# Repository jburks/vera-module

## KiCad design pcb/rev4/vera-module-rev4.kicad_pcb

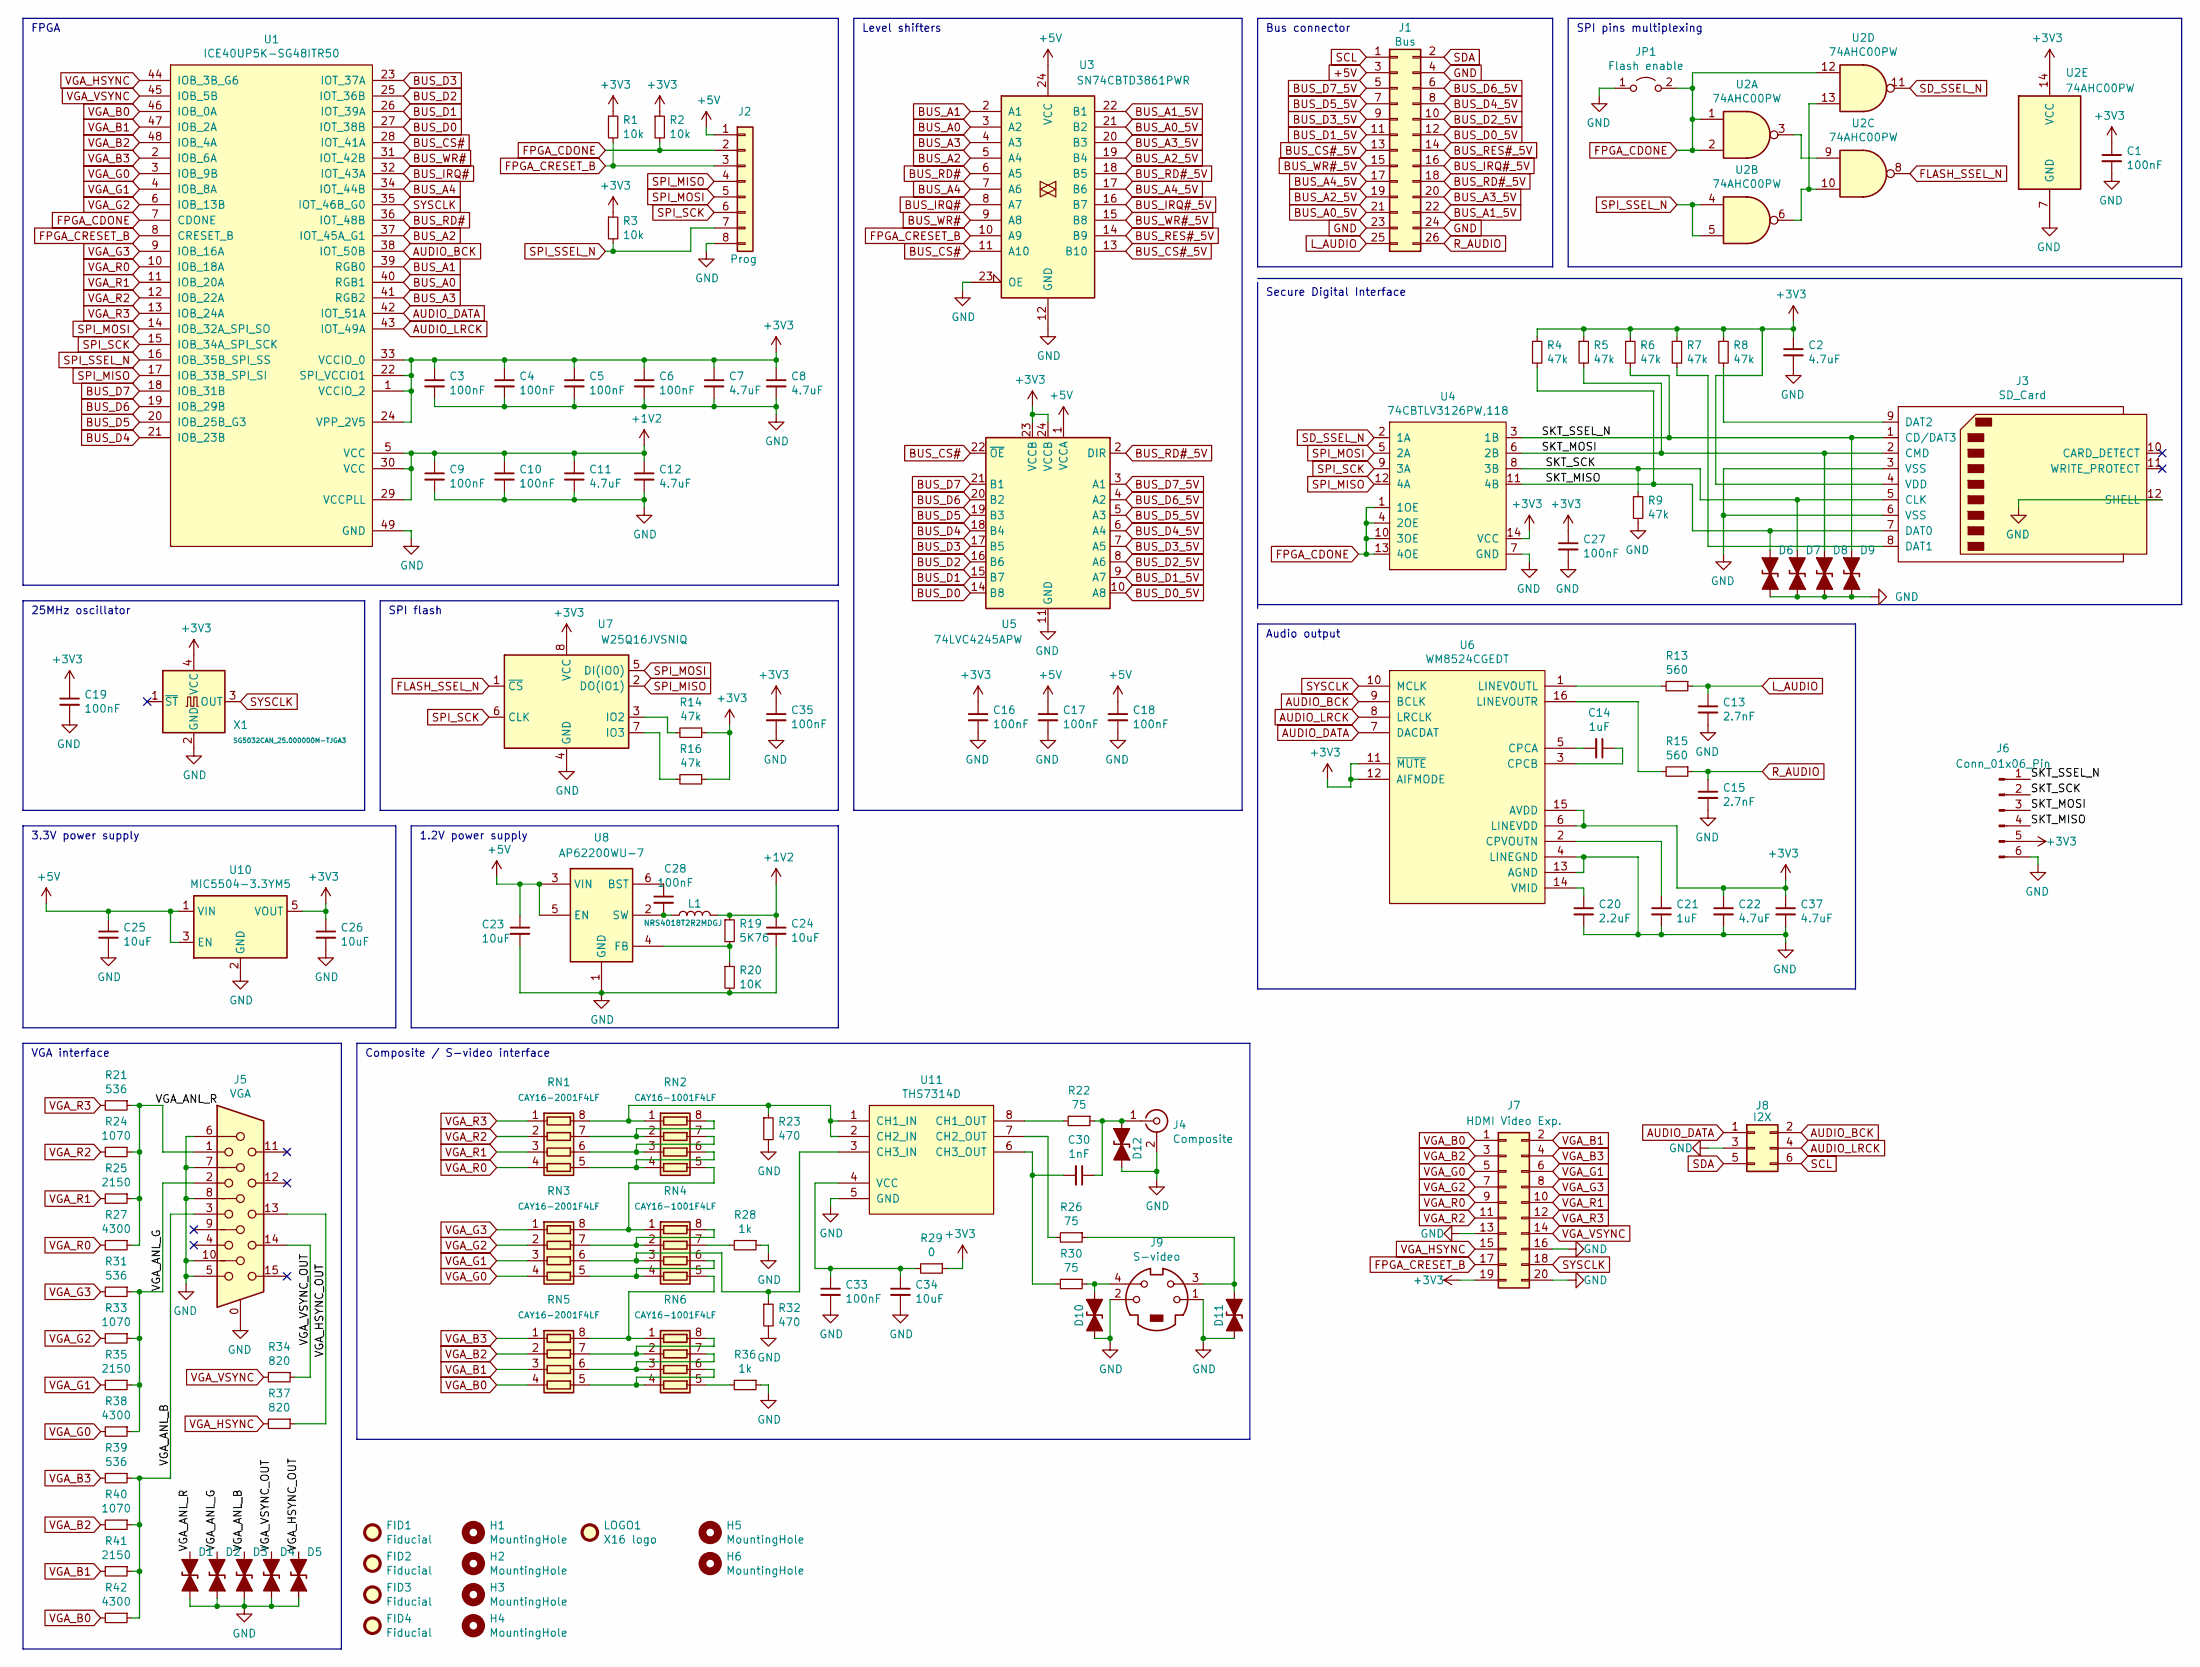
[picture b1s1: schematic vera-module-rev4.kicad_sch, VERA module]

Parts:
C1, C3, C4, C5, C6, C9, C10, C16, C17, C18, C19, C27, C28, C33, C35: 100nF; C_0603_1608Metric
C2, C7, C8, C11, C12, C22, C37: 4.7uF; C_0603_1608Metric
C13, C15: 2.7nF; C_0603_1608Metric
C14, C21: 1uF; C_0603_1608Metric
C20: 2.2uF; C_0603_1608Metric
C23, C24, C25, C26, C34: 10uF; C_0805_2012Metric
C30: 1nF; C_0603_1608Metric
D1, D2, D3, D4, D5, D6, D7, D8, D9, D10, D11, D12: D_TVS_Filled; D_0603_1608Metric
FID1, FID2, FID3, FID4: Fiducial; Fiducial_1mm_Mask2mm
H1, H2, H3, H4: MountingHole; MountingHole_3.2mm_M3
H5, H6: MountingHole; MountingHole_2.2mm_M2
J1: Bus; PinHeader_2x13_P2.54mm_Vertical
J2: Prog; PinHeader_1x08_P2.54mm_Vertical
J3: SD_Card; SD-102
J4: Composite; AV-5
J5: VGA; ICD15S13E4GV00LF
J6: Conn_01x06_Pin; PinHeader_1x06_P2.54mm_Vertical
J7: HDMI Video Exp.; PinSocket_2x10_P2.00mm_Vertical_SMD
J8: I2X; PinSocket_2x03_P2.00mm_Vertical
J9: S-video; MDC-4-02
JP1: Flash enable; PinHeader_1x02_P2.54mm_Vertical
L1: NRS4018T2R2MDGJ; L_Bourns-SRN4018
LOGO1: X16 logo; VERA_CE_Logo2
R1, R2, R3: 10k; R_0603_1608Metric
R4, R5, R6, R7, R8, R9, R14, R16: 47k; R_0603_1608Metric
R13, R15: 560; R_0603_1608Metric
R19: 5K76; R_0603_1608Metric
R20: 10K; R_0603_1608Metric
R21, R31, R39: 536; R_0603_1608Metric
R22, R26, R30: 75; R_0603_1608Metric
R23, R32: 470; R_0603_1608Metric
R24, R33, R40: 1070; R_0603_1608Metric
R25, R35, R41: 2150; R_0603_1608Metric
R27, R38, R42: 4300; R_0603_1608Metric
R28, R36: 1k; R_0603_1608Metric
R29: 0; R_0603_1608Metric
R34, R37: 820; R_0603_1608Metric
RN1, RN3, RN5: CAY16-2001F4LF; R_Array_Convex_4x0603
RN2, RN4, RN6: CAY16-1001F4LF; R_Array_Convex_4x0603
U1: ICE40UP5K-SG48ITR50; QFN-48-1EP_7x7mm_P0.5mm_EP5.3x5.3mm
U2: 74AHC00PW; TSSOP-14_4.4x5mm_P0.65mm
U3: SN74CBTD3861PWR; TSSOP-24_4.4x7.8mm_P0.65mm
U4: 74CBTLV3126PW,118; TSSOP-14_4.4x5mm_P0.65mm
U5: 74LVC4245APW; TSSOP-24_4.4x7.8mm_P0.65mm
U6: WM8524CGEDT; TSSOP-16_4.4x5mm_P0.65mm
U7: W25Q16JVSNIQ; SOIC-8_3.9x4.9mm_P1.27mm
U8: AP62200WU-7; TSOT26-6; Mouser Part Number 621-AP62200WU-7
U10: MIC5504-3.3YM5; SOT-23-5
U11: THS7314D; SOIC-8_3.9x4.9mm_P1.27mm
X1: SG5032CAN_25.000000M-TJGA3; Oscillator_SMD_SeikoEpson_SG8002LB-4Pin_5.0x3.2mm

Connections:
+1V2: C9.1, C10.1, C11.1, C12.1, C24.1, L1.2, R19.1, U1.5 (VCC), U1.29 (VCCPLL), U1.30 (VCC)
+3V3: C1.1, C2.1, C3.1, C4.1, C5.1, C6.1, C7.1, C8.1, C16.1, C19.1, C22.1, C26.1, C27.1, C35.1, C37.1, J3.4 (VDD), J6.5, J7.19, R1.1, R2.1, R3.1, R4.1, R5.1, R6.1, R7.1, R8.1, R14.1, R16.1, R29.1, U1.1 (VCCIO_2), U1.22 (SPI_VCCIO1), U1.24 (VPP_2V5), U1.33 (VCCIO_0), U2.14 (VCC), U4.14 (VCC), U5.23 (VCCB), U5.24 (VCCB), U6.6 (LINEVDD), U6.11 (~MUTE), U6.12 (AIFMODE), U6.15 (AVDD), U7.8 (VCC), U10.5 (VOUT), X1.4 (VCC)
+5V: C17.1, C18.1, C23.1, C25.1, J1.3, J2.1, U3.24 (VCC), U5.1 (VCCA), U8.3 (VIN), U8.5 (EN), U10.1 (VIN), U10.3 (EN)
/SKT_MISO: D6.2 (A2), J3.7 (DAT0), J6.4, R4.2, U4.11 (4B)
/SKT_MOSI: D8.2 (A2), J3.2 (CMD), J6.3, R5.2, U4.6 (2B)
/SKT_SCK: D7.2 (A2), J3.5 (CLK), J6.2, R9.1, U4.8 (3B)
/SKT_SSEL_N: D9.2 (A2), J3.1 (CD/DAT3), J6.1, R6.2, U4.3 (1B)
/VGA_ANL_B: D3.2 (A2), J5.3, R39.1, R40.1, R41.1, R42.1
/VGA_ANL_G: D2.2 (A2), J5.2, R31.1, R33.1, R35.1, R38.1
/VGA_ANL_R: D1.2 (A2), J5.1, R21.1, R24.1, R25.1, R27.1
/VGA_HSYNC_OUT: D5.2 (A2), J5.13, R37.1
/VGA_VSYNC_OUT: D4.2 (A2), J5.14, R34.1
AUDIO_BCK: J8.2, U1.38 (IOT_50B), U6.9 (BCLK)
AUDIO_DATA: J8.1, U1.42 (IOT_51A), U6.7 (DACDAT)
AUDIO_LRCK: J8.4, U1.43 (IOT_49A), U6.8 (LRCLK)
BUS_A0: U1.40 (RGB1), U3.3 (A2)
BUS_A0_5V: J1.21, U3.21 (B2)
BUS_A1: U1.39 (RGB0), U3.2 (A1)
BUS_A1_5V: J1.22, U3.22 (B1)
BUS_A2: U1.37 (IOT_45A_G1), U3.5 (A4)
BUS_A2_5V: J1.19, U3.19 (B4)
BUS_A3: U1.41 (RGB2), U3.4 (A3)
BUS_A3_5V: J1.20, U3.20 (B3)
BUS_A4: U1.34 (IOT_44B), U3.7 (A6)
BUS_A4_5V: J1.17, U3.17 (B6)
BUS_CS#: U1.28 (IOT_41A), U3.11 (A10), U5.22 (~OE)
BUS_CS#_5V: J1.13, U3.13 (B10)
BUS_D0: U1.27 (IOT_38B), U5.14 (B8)
BUS_D0_5V: J1.12, U5.10 (A8)
BUS_D1: U1.26 (IOT_39A), U5.15 (B7)
BUS_D1_5V: J1.11, U5.9 (A7)
BUS_D2: U1.25 (IOT_36B), U5.16 (B6)
BUS_D2_5V: J1.10, U5.8 (A6)
BUS_D3: U1.23 (IOT_37A), U5.17 (B5)
BUS_D3_5V: J1.9, U5.7 (A5)
BUS_D4: U1.21 (IOB_23B), U5.18 (B4)
BUS_D4_5V: J1.8, U5.6 (A4)
BUS_D5: U1.20 (IOB_25B_G3), U5.19 (B3)
BUS_D5_5V: J1.7, U5.5 (A3)
BUS_D6: U1.19 (IOB_29B), U5.20 (B2)
BUS_D6_5V: J1.6, U5.4 (A2)
BUS_D7: U1.18 (IOB_31B), U5.21 (B1)
BUS_D7_5V: J1.5, U5.3 (A1)
BUS_IRQ#: U1.32 (IOT_43A), U3.8 (A7)
BUS_IRQ#_5V: J1.16, U3.16 (B7)
BUS_RD#: U1.36 (IOT_48B), U3.6 (A5)
BUS_RD#_5V: J1.18, U3.18 (B5), U5.2 (DIR)
BUS_RES#_5V: J1.14, U3.14 (B9)
BUS_WR#: U1.31 (IOT_42B), U3.9 (A8)
BUS_WR#_5V: J1.15, U3.15 (B8)
FLASH_SSEL_N: U2.8, U7.1 (~CS)
FPGA_CDONE: J2.2, JP1.2 (B), R2.2, U1.7 (CDONE), U2.1, U2.2, U2.12, U4.1 (1OE), U4.4 (2OE), U4.10 (3OE), U4.13 (4OE)
FPGA_CRESET_B: J2.3, J7.17, R1.2, U1.8 (CRESET_B), U3.10 (A9)
GND: C1.2, C2.2, C3.2, C4.2, C5.2, C6.2, C7.2, C8.2, C9.2, C10.2, C11.2, C12.2, C13.2, C15.2, C16.2, C17.2, C18.2, C19.2, C20.2, C21.2, C22.2, C23.2, C24.2, C25.2, C26.2, C27.2, C33.2, C34.2, C35.2, C37.2, D1.1 (A1), D2.1 (A1), D3.1 (A1), D4.1 (A1), D5.1 (A1), D6.1 (A1), D7.1 (A1), D8.1 (A1), D9.1 (A1), D10.1 (A1), D11.1 (A1), D12.1 (A1), J1.4, J1.23, J1.24, J2.8, J3.3 (VSS), J3.6 (VSS), J3.12 (SHELL), J4.2 (Ext), J5.0, J5.5, J5.6, J5.7, J5.8, J5.10, J6.6, J7.13, J7.16, J7.20, J8.3, J9.1, J9.2, JP1.1 (A), R9.2, R20.2, R23.2, R28.1, R32.2, R36.1, U1.49 (GND), U2.7 (GND), U3.12 (GND), U3.23 (OE), U4.7 (GND), U5.11 (GND), U5.12 (GND), U5.13 (GND), U6.4 (LINEGND), U6.13 (AGND), U7.4 (GND), U8.1 (GND), U10.2 (GND), U11.5 (GND), X1.2 (GND)
L_AUDIO: C13.1, J1.25, R13.1
unnamed: D10.2 (A2), J9.4, R30.1
unnamed: D11.2 (A2), J9.3, R26.1
unnamed: C30.1, D12.2 (A2), J4.1 (In), R22.1
unnamed: J3.8 (DAT1), R7.2
unnamed: J3.9 (DAT2), R8.2
unnamed: R23.1, RN1.8 (R1.2), RN2.1 (R1.1), U11.1 (CH1_IN), U11.2 (CH2_IN)
unnamed: RN1.7 (R2.2), RN2.2 (R2.1), RN2.8 (R1.2)
unnamed: RN1.6 (R3.2), RN2.3 (R3.1), RN2.7 (R2.2)
unnamed: RN1.5 (R4.2), RN2.4 (R4.1), RN2.6 (R3.2)
unnamed: RN2.5 (R4.2), RN3.8 (R1.2), RN4.1 (R1.1)
unnamed: RN3.7 (R2.2), RN4.2 (R2.1), RN4.8 (R1.2)
unnamed: R32.1, RN3.6 (R3.2), RN4.3 (R3.1), U11.3 (CH3_IN)
unnamed: RN3.5 (R4.2), RN4.4 (R4.1), RN4.6 (R3.2)
unnamed: R28.2, RN4.7 (R2.2)
unnamed: RN4.5 (R4.2), RN5.8 (R1.2), RN6.1 (R1.1)
unnamed: RN5.7 (R2.2), RN6.2 (R2.1), RN6.8 (R1.2)
unnamed: RN5.6 (R3.2), RN6.3 (R3.1), RN6.7 (R2.2)
unnamed: RN5.5 (R4.2), RN6.4 (R4.1), RN6.6 (R3.2)
unnamed: R36.2, RN6.5 (R4.2)
unnamed: U2.3, U2.9
unnamed: U2.6, U2.10, U2.13
unnamed: C14.2, U6.5 (CPCA)
unnamed: C14.1, U6.3 (CPCB)
unnamed: C21.1, U6.2 (CPVOUTN)
unnamed: R13.2, U6.1 (LINEVOUTL)
unnamed: R15.2, U6.16 (LINEVOUTR)
unnamed: C20.1, U6.14 (VMID)
unnamed: R14.2, U7.3 (IO2)
unnamed: R16.2, U7.7 (IO3)
unnamed: C28.1, U8.6 (BST)
unnamed: R19.2, R20.1, U8.4 (FB)
unnamed: C28.2, L1.1, U8.2 (SW)
unnamed: R22.2, U11.8 (CH1_OUT)
unnamed: R26.2, U11.7 (CH2_OUT)
unnamed: C30.2, R30.2, U11.6 (CH3_OUT)
unnamed: C33.1, C34.1, R29.2, U11.4 (VCC)
R_AUDIO: C15.1, J1.26, R15.1
SCL: J1.1, J8.6
SDA: J1.2, J8.5
SD_SSEL_N: U2.11, U4.2 (1A)
SPI_MISO: J2.4, U1.17 (IOB_33B_SPI_SI), U4.12 (4A), U7.2 (DO(IO1))
SPI_MOSI: J2.5, U1.14 (IOB_32A_SPI_SO), U4.5 (2A), U7.5 (DI(IO0))
SPI_SCK: J2.6, U1.15 (IOB_34A_SPI_SCK), U4.9 (3A), U7.6 (CLK)
SPI_SSEL_N: J2.7, R3.2, U1.16 (IOB_35B_SPI_SS), U2.4, U2.5
SYSCLK: J7.18, U1.35 (IOT_46B_G0), U6.10 (MCLK), X1.3 (OUT)
VGA_B0: J7.1, R42.2, RN5.4 (R4.1), U1.46 (IOB_0A)
VGA_B1: J7.2, R41.2, RN5.3 (R3.1), U1.47 (IOB_2A)
VGA_B2: J7.3, R40.2, RN5.2 (R2.1), U1.48 (IOB_4A)
VGA_B3: J7.4, R39.2, RN5.1 (R1.1), U1.2 (IOB_6A)
VGA_G0: J7.5, R38.2, RN3.4 (R4.1), U1.3 (IOB_9B)
VGA_G1: J7.6, R35.2, RN3.3 (R3.1), U1.4 (IOB_8A)
VGA_G2: J7.7, R33.2, RN3.2 (R2.1), U1.6 (IOB_13B)
VGA_G3: J7.8, R31.2, RN3.1 (R1.1), U1.9 (IOB_16A)
VGA_HSYNC: J7.15, R37.2, U1.44 (IOB_3B_G6)
VGA_R0: J7.9, R27.2, RN1.4 (R4.1), U1.10 (IOB_18A)
VGA_R1: J7.10, R25.2, RN1.3 (R3.1), U1.11 (IOB_20A)
VGA_R2: J7.11, R24.2, RN1.2 (R2.1), U1.12 (IOB_22A)
VGA_R3: J7.12, R21.2, RN1.1 (R1.1), U1.13 (IOB_24A)
VGA_VSYNC: J7.14, R34.2, U1.45 (IOB_5B)

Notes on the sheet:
Composite / S-video interface
1.2V power supply
25MHz oscillator
Secure Digital Interface
3.3V power supply
Audio output
SPI flash
FPGA
SPI pins multiplexing
Level shifters
VGA interface
Bus connector

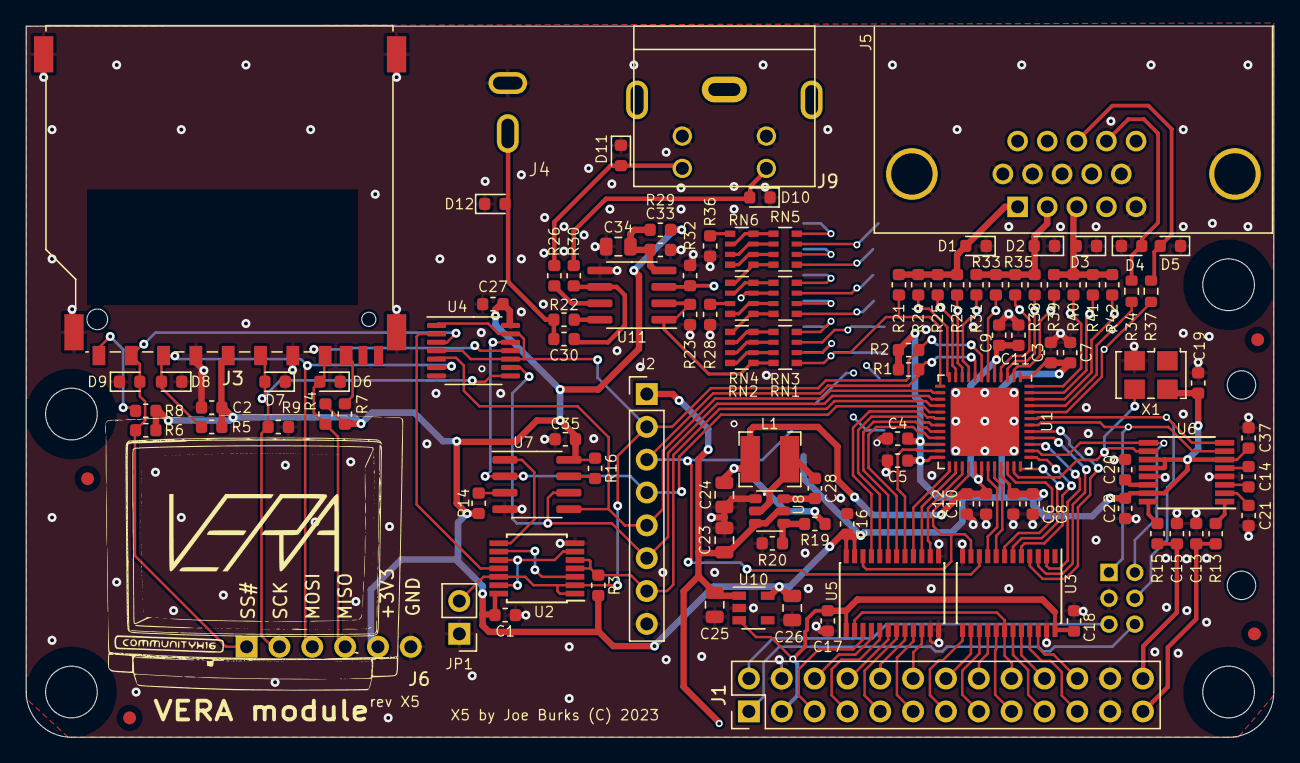
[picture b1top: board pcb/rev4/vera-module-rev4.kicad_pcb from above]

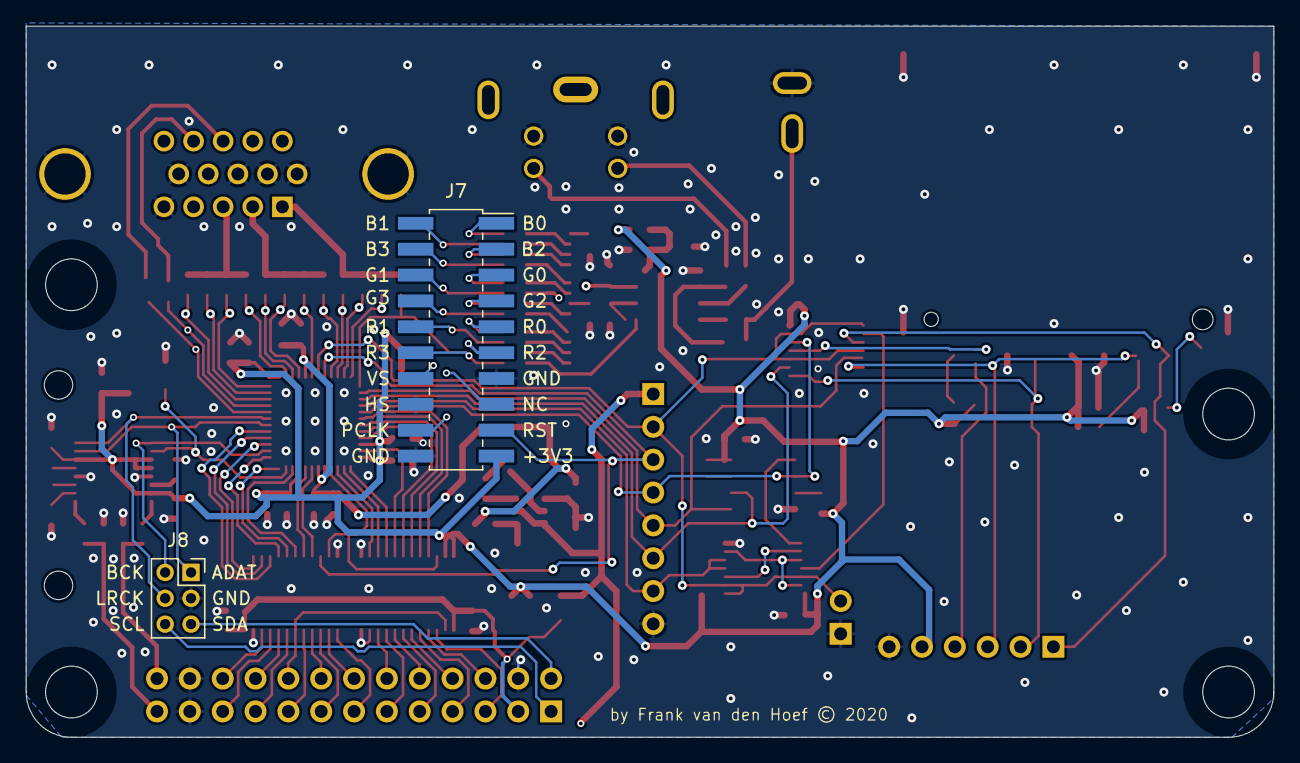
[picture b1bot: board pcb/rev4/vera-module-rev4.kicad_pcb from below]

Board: 4 copper layers, 96.5 x 55.0 mm, 121 parts (2 on the bottom side), 114 nets.

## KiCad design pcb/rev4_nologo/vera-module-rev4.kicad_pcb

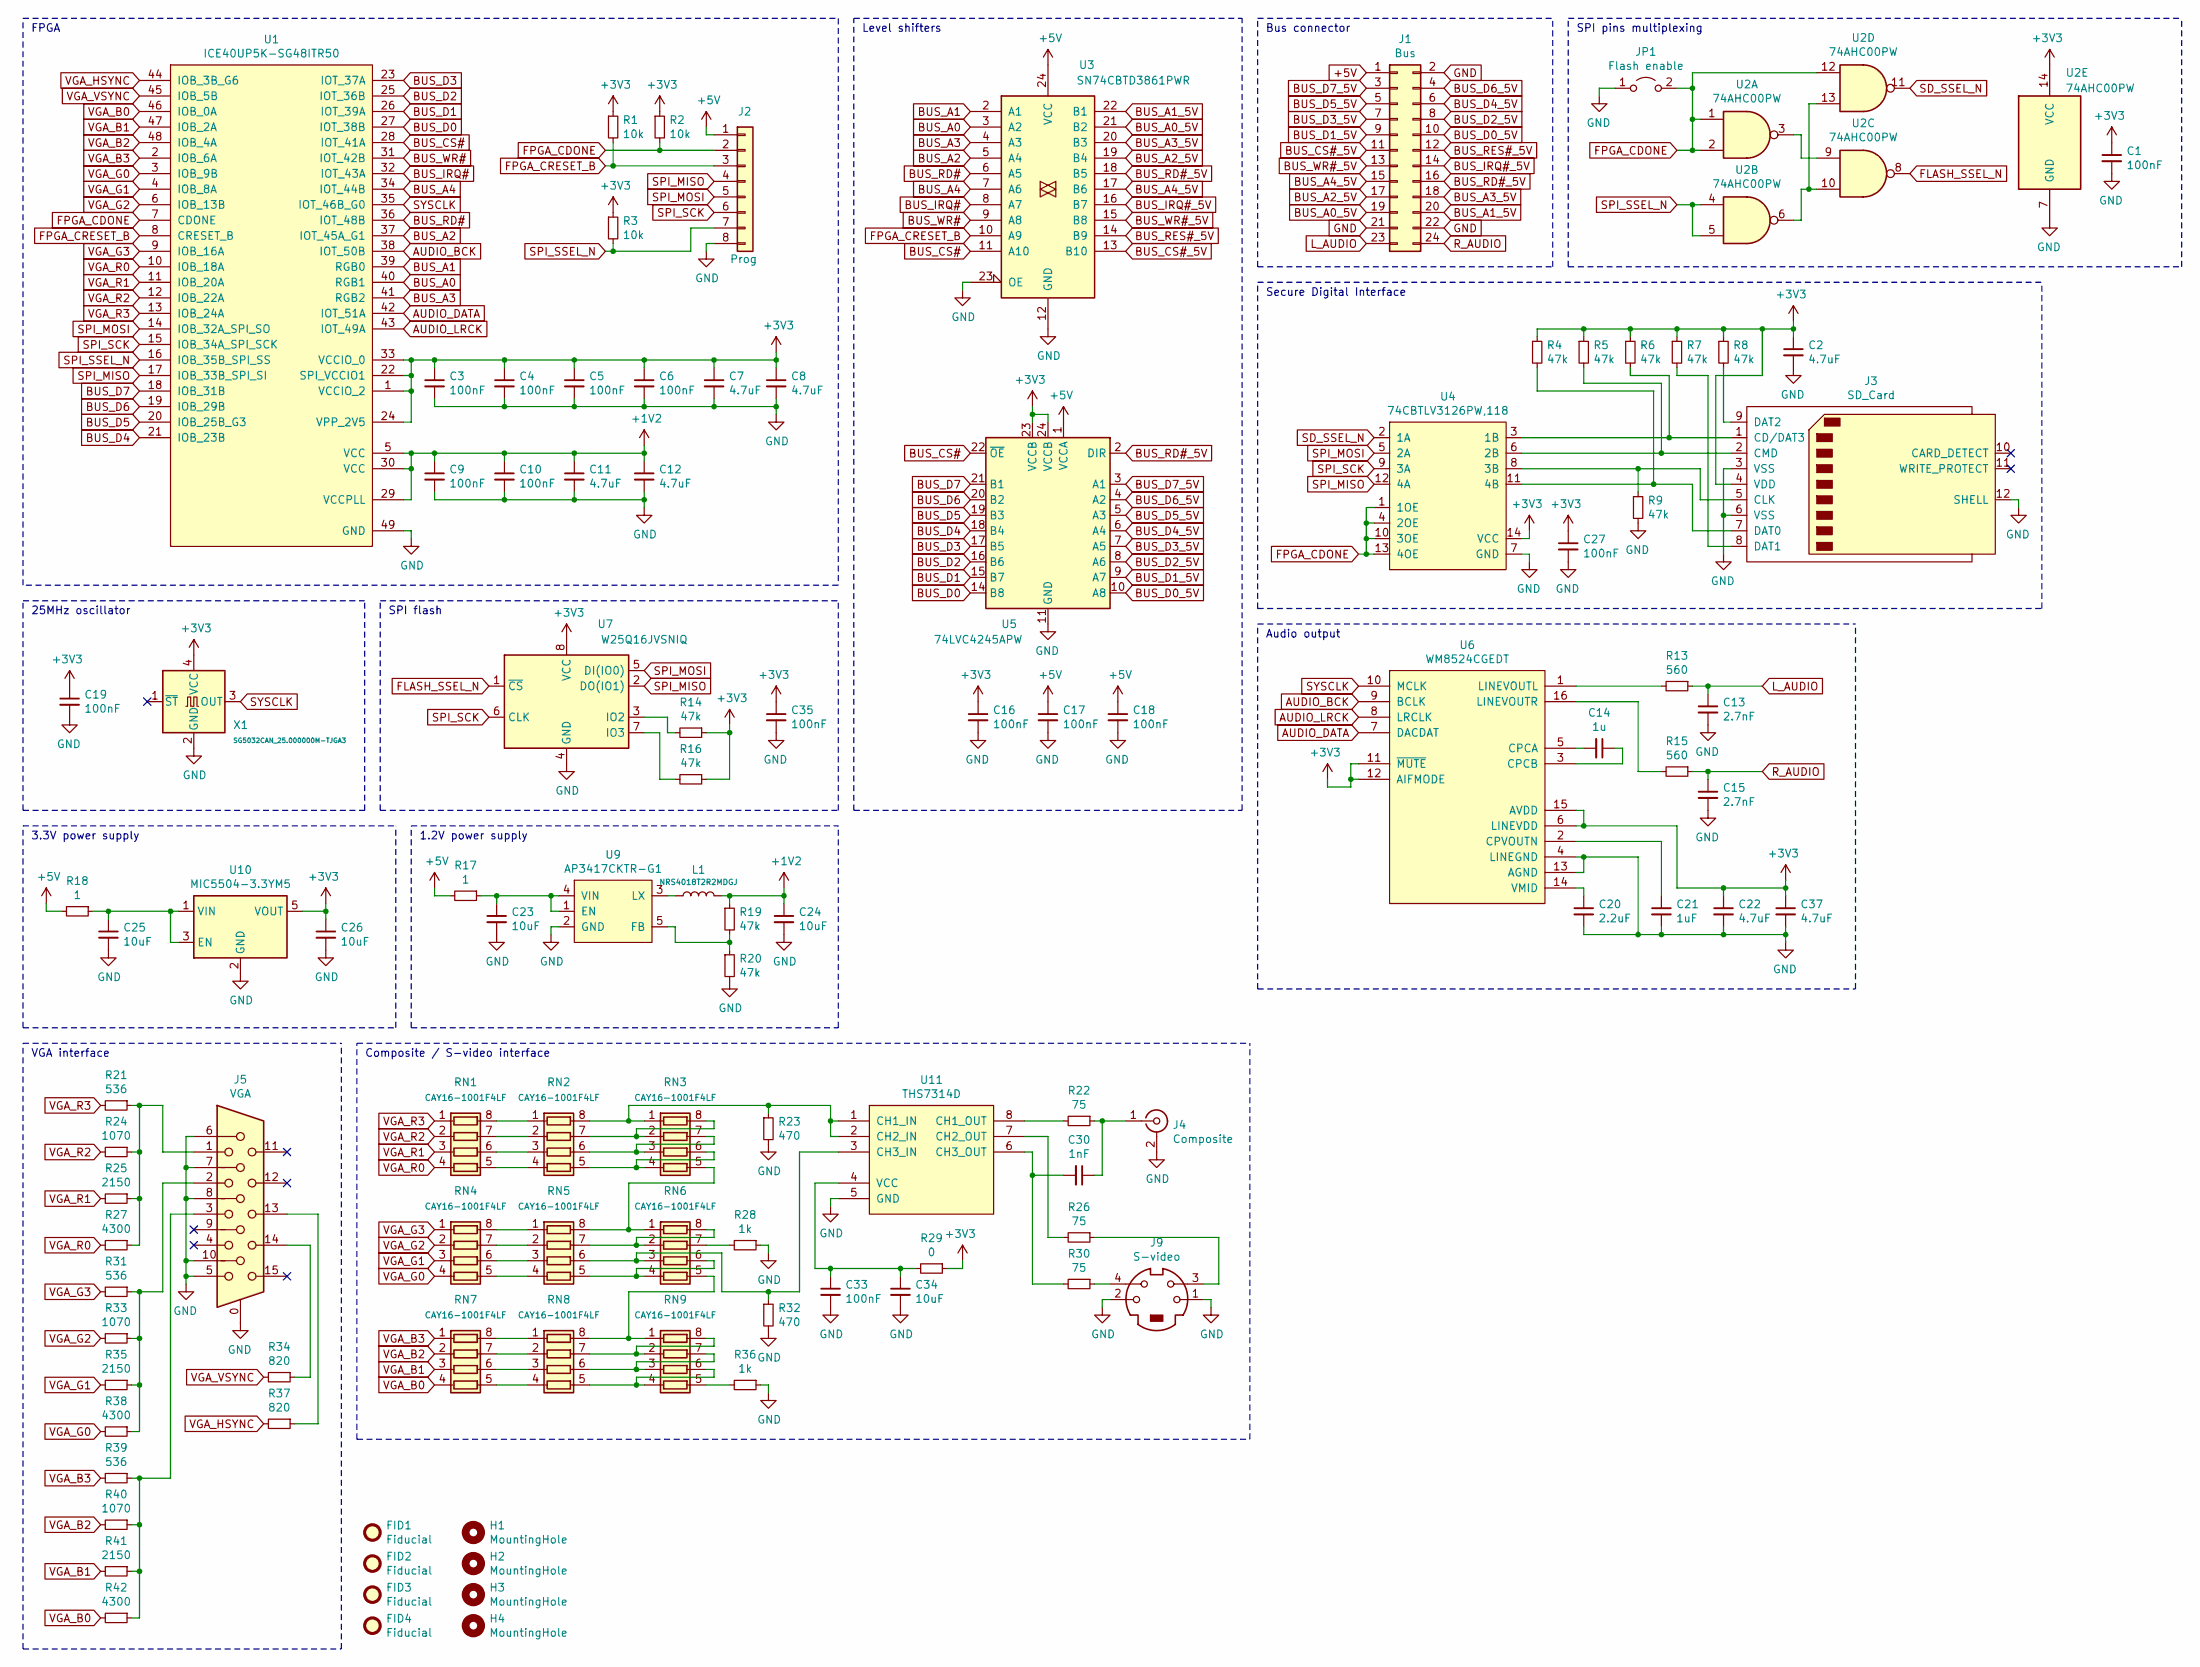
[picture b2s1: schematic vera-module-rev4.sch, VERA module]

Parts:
C1, C3, C4, C5, C6, C9, C10, C16, C17, C18, C19, C27, C33, C35: 100nF; C_0603_1608Metric
C2, C7, C8, C11, C12, C22, C37: 4.7uF; C_0603_1608Metric
C13, C15: 2.7nF; C_0603_1608Metric
C14: 1u; C_0603_1608Metric
C20: 2.2uF; C_0603_1608Metric
C21: 1uF; C_0603_1608Metric
C23, C24, C25, C26, C34: 10uF; C_0805_2012Metric
C30: 1nF; C_0603_1608Metric
FID1, FID2, FID3, FID4: Fiducial; Fiducial_1mm_Mask2mm
H1, H2, H3, H4: MountingHole; MountingHole_3.2mm_M3
J1: Bus; PinHeader_2x12_P2.54mm_Vertical
J2: Prog; PinHeader_1x08_P2.54mm_Vertical
J3: SD_Card; SD_TE_2041021
J4: Composite; RCJ-014
J5: VGA; ICD15S13E4GV00LF
J9: S-video; MD-40S
JP1: Flash enable; PinHeader_1x02_P2.54mm_Vertical
L1: NRS4018T2R2MDGJ; L_Bourns-SRN4018
R1, R2, R3: 10k; R_0603_1608Metric
R4, R5, R6, R7, R8, R9, R14, R16, R19, R20: 47k; R_0603_1608Metric
R13, R15: 560; R_0603_1608Metric
R17, R18: 1; R_0603_1608Metric
R21, R31, R39: 536; R_0603_1608Metric
R22, R26, R30: 75; R_0603_1608Metric
R23, R32: 470; R_0603_1608Metric
R24, R33, R40: 1070; R_0603_1608Metric
R25, R35, R41: 2150; R_0603_1608Metric
R27, R38, R42: 4300; R_0603_1608Metric
R28, R36: 1k; R_0603_1608Metric
R29: 0; R_0603_1608Metric
R34, R37: 820; R_0603_1608Metric
RN1, RN2, RN3, RN4, RN5, RN6, RN7, RN8, RN9: CAY16-1001F4LF; R_Array_Convex_4x0603
U1: ICE40UP5K-SG48ITR50; QFN-48-1EP_7x7mm_P0.5mm_EP5.3x5.3mm
U2: 74AHC00PW; TSSOP-14_4.4x5mm_P0.65mm
U3: SN74CBTD3861PWR; TSSOP-24_4.4x7.8mm_P0.65mm
U4: 74CBTLV3126PW,118; TSSOP-14_4.4x5mm_P0.65mm
U5: 74LVC4245APW; TSSOP-24_4.4x7.8mm_P0.65mm
U6: WM8524CGEDT; TSSOP-16_4.4x5mm_P0.65mm
U7: W25Q16JVSNIQ; SOIC-8_3.9x4.9mm_P1.27mm
U9: AP3417CKTR-G1; SOT-23-5
U10: MIC5504-3.3YM5; SOT-23-5
U11: THS7314D; SOIC-8_3.9x4.9mm_P1.27mm
X1: SG5032CAN_25.000000M-TJGA3; Oscillator_SMD_SeikoEpson_SG8002LB-4Pin_5.0x3.2mm

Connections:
+1V2: C9.1, C10.1, C11.1, C12.1, C24.1, L1.2, R19.1, U1.5 (VCC), U1.29 (VCCPLL), U1.30 (VCC)
+3V3: C1.1, C2.1, C3.1, C4.1, C5.1, C6.1, C7.1, C8.1, C16.1, C19.1, C22.1, C26.1, C27.1, C35.1, C37.1, J3.4 (VDD), R1.1, R2.1, R3.1, R4.1, R5.1, R6.1, R7.1, R8.1, R14.1, R16.1, R29.1, U1.1 (VCCIO_2), U1.22 (SPI_VCCIO1), U1.24 (VPP_2V5), U1.33 (VCCIO_0), U2.14 (VCC), U4.14 (VCC), U5.23 (VCCB), U5.24 (VCCB), U6.6 (LINEVDD), U6.11 (~MUTE), U6.12 (AIFMODE), U6.15 (AVDD), U7.8 (VCC), U10.5 (VOUT), X1.4 (VCC)
+5V: C17.1, C18.1, J1.1, J2.1, R17.2, R18.2, U3.24 (VCC), U5.1 (VCCA)
AUDIO_BCK: U1.38 (IOT_50B), U6.9 (BCLK)
AUDIO_DATA: U1.42 (IOT_51A), U6.7 (DACDAT)
AUDIO_LRCK: U1.43 (IOT_49A), U6.8 (LRCLK)
BUS_A0: U1.40 (RGB1), U3.3 (A2)
BUS_A0_5V: J1.19, U3.21 (B2)
BUS_A1: U1.39 (RGB0), U3.2 (A1)
BUS_A1_5V: J1.20, U3.22 (B1)
BUS_A2: U1.37 (IOT_45A_G1), U3.5 (A4)
BUS_A2_5V: J1.17, U3.19 (B4)
BUS_A3: U1.41 (RGB2), U3.4 (A3)
BUS_A3_5V: J1.18, U3.20 (B3)
BUS_A4: U1.34 (IOT_44B), U3.7 (A6)
BUS_A4_5V: J1.15, U3.17 (B6)
BUS_CS#: U1.28 (IOT_41A), U3.11 (A10), U5.22 (~OE)
BUS_CS#_5V: J1.11, U3.13 (B10)
BUS_D0: U1.27 (IOT_38B), U5.14 (B8)
BUS_D0_5V: J1.10, U5.10 (A8)
BUS_D1: U1.26 (IOT_39A), U5.15 (B7)
BUS_D1_5V: J1.9, U5.9 (A7)
BUS_D2: U1.25 (IOT_36B), U5.16 (B6)
BUS_D2_5V: J1.8, U5.8 (A6)
BUS_D3: U1.23 (IOT_37A), U5.17 (B5)
BUS_D3_5V: J1.7, U5.7 (A5)
BUS_D4: U1.21 (IOB_23B), U5.18 (B4)
BUS_D4_5V: J1.6, U5.6 (A4)
BUS_D5: U1.20 (IOB_25B_G3), U5.19 (B3)
BUS_D5_5V: J1.5, U5.5 (A3)
BUS_D6: U1.19 (IOB_29B), U5.20 (B2)
BUS_D6_5V: J1.4, U5.4 (A2)
BUS_D7: U1.18 (IOB_31B), U5.21 (B1)
BUS_D7_5V: J1.3, U5.3 (A1)
BUS_IRQ#: U1.32 (IOT_43A), U3.8 (A7)
BUS_IRQ#_5V: J1.14, U3.16 (B7)
BUS_RD#: U1.36 (IOT_48B), U3.6 (A5)
BUS_RD#_5V: J1.16, U3.18 (B5), U5.2 (DIR)
BUS_RES#_5V: J1.12, U3.14 (B9)
BUS_WR#: U1.31 (IOT_42B), U3.9 (A8)
BUS_WR#_5V: J1.13, U3.15 (B8)
FLASH_SSEL_N: U2.8, U7.1 (~CS)
FPGA_CDONE: J2.2, JP1.2 (B), R2.2, U1.7 (CDONE), U2.1, U2.2, U2.12, U4.1 (1OE), U4.4 (2OE), U4.10 (3OE), U4.13 (4OE)
FPGA_CRESET_B: J2.3, R1.2, U1.8 (CRESET_B), U3.10 (A9)
GND: C1.2, C2.2, C3.2, C4.2, C5.2, C6.2, C7.2, C8.2, C9.2, C10.2, C11.2, C12.2, C13.2, C15.2, C16.2, C17.2, C18.2, C19.2, C20.2, C21.2, C22.2, C23.2, C24.2, C25.2, C26.2, C27.2, C33.2, C34.2, C35.2, C37.2, J1.2, J1.21, J1.22, J2.8, J3.3 (VSS), J3.6 (VSS), J3.12 (SHELL), J4.2 (Ext), J5.0, J5.5, J5.6, J5.7, J5.8, J5.10, J9.1, J9.2, JP1.1 (A), R9.2, R20.2, R23.2, R28.1, R32.2, R36.1, U1.49 (GND), U2.7 (GND), U3.12 (GND), U3.23 (OE), U4.7 (GND), U5.11 (GND), U5.12 (GND), U5.13 (GND), U6.4 (LINEGND), U6.13 (AGND), U7.4 (GND), U9.2 (GND), U10.2 (GND), U11.5 (GND), X1.2 (GND)
L_AUDIO: C13.1, J1.23, R13.1
unnamed: C14.1, U6.3 (CPCB)
unnamed: C14.2, U6.5 (CPCA)
unnamed: C20.1, U6.14 (VMID)
unnamed: C21.1, U6.2 (CPVOUTN)
unnamed: C23.1, R17.1, U9.1 (EN), U9.4 (VIN)
unnamed: C25.1, R18.1, U10.1 (VIN), U10.3 (EN)
unnamed: C30.1, J4.1 (In), R22.1
unnamed: C30.2, R30.2, U11.6 (CH3_OUT)
unnamed: C33.1, C34.1, R29.2, U11.4 (VCC)
unnamed: J3.1 (CD/DAT3), R6.2, U4.3 (1B)
unnamed: J3.2 (CMD), R5.2, U4.6 (2B)
unnamed: J3.5 (CLK), R9.1, U4.8 (3B)
unnamed: J3.7 (DAT0), R4.2, U4.11 (4B)
unnamed: J3.8 (DAT1), R7.2
unnamed: J3.9 (DAT2), R8.2
unnamed: J5.1, R21.1, R24.1, R25.1, R27.1
unnamed: J5.2, R31.1, R33.1, R35.1, R38.1
unnamed: J5.3, R39.1, R40.1, R41.1, R42.1
unnamed: J5.13, R37.1
unnamed: J5.14, R34.1
unnamed: J9.3, R26.1
unnamed: J9.4, R30.1
unnamed: L1.1, U9.3 (LX)
unnamed: R13.2, U6.1 (LINEVOUTL)
unnamed: R14.2, U7.3 (IO2)
unnamed: R15.2, U6.16 (LINEVOUTR)
unnamed: R16.2, U7.7 (IO3)
unnamed: R19.2, R20.1, U9.5 (FB)
unnamed: R22.2, U11.8 (CH1_OUT)
unnamed: R23.1, RN2.8 (R1.2), RN3.1 (R1.1), U11.1 (CH1_IN), U11.2 (CH2_IN)
unnamed: R26.2, U11.7 (CH2_OUT)
unnamed: R28.2, RN6.7 (R2.2)
unnamed: R32.1, RN5.6 (R3.2), RN6.3 (R3.1), U11.3 (CH3_IN)
unnamed: R36.2, RN9.5 (R4.2)
unnamed: RN1.5 (R4.2), RN2.4 (R4.1)
unnamed: RN1.6 (R3.2), RN2.3 (R3.1)
unnamed: RN1.7 (R2.2), RN2.2 (R2.1)
unnamed: RN1.8 (R1.2), RN2.1 (R1.1)
unnamed: RN2.5 (R4.2), RN3.4 (R4.1), RN3.6 (R3.2)
unnamed: RN2.6 (R3.2), RN3.3 (R3.1), RN3.7 (R2.2)
unnamed: RN2.7 (R2.2), RN3.2 (R2.1), RN3.8 (R1.2)
unnamed: RN3.5 (R4.2), RN5.8 (R1.2), RN6.1 (R1.1)
unnamed: RN4.5 (R4.2), RN5.4 (R4.1)
unnamed: RN4.6 (R3.2), RN5.3 (R3.1)
unnamed: RN4.7 (R2.2), RN5.2 (R2.1)
unnamed: RN4.8 (R1.2), RN5.1 (R1.1)
unnamed: RN5.5 (R4.2), RN6.4 (R4.1), RN6.6 (R3.2)
unnamed: RN5.7 (R2.2), RN6.2 (R2.1), RN6.8 (R1.2)
unnamed: RN6.5 (R4.2), RN8.8 (R1.2), RN9.1 (R1.1)
unnamed: RN7.5 (R4.2), RN8.4 (R4.1)
unnamed: RN7.6 (R3.2), RN8.3 (R3.1)
unnamed: RN7.7 (R2.2), RN8.2 (R2.1)
unnamed: RN7.8 (R1.2), RN8.1 (R1.1)
unnamed: RN8.5 (R4.2), RN9.4 (R4.1), RN9.6 (R3.2)
unnamed: RN8.6 (R3.2), RN9.3 (R3.1), RN9.7 (R2.2)
unnamed: RN8.7 (R2.2), RN9.2 (R2.1), RN9.8 (R1.2)
unnamed: U2.3, U2.9
unnamed: U2.6, U2.10, U2.13
R_AUDIO: C15.1, J1.24, R15.1
SD_SSEL_N: U2.11, U4.2 (1A)
SPI_MISO: J2.4, U1.17 (IOB_33B_SPI_SI), U4.12 (4A), U7.2 (DO(IO1))
SPI_MOSI: J2.5, U1.14 (IOB_32A_SPI_SO), U4.5 (2A), U7.5 (DI(IO0))
SPI_SCK: J2.6, U1.15 (IOB_34A_SPI_SCK), U4.9 (3A), U7.6 (CLK)
SPI_SSEL_N: J2.7, R3.2, U1.16 (IOB_35B_SPI_SS), U2.4, U2.5
SYSCLK: U1.35 (IOT_46B_G0), U6.10 (MCLK), X1.3 (OUT)
VGA_B0: R42.2, RN7.4 (R4.1), U1.46 (IOB_0A)
VGA_B1: R41.2, RN7.3 (R3.1), U1.47 (IOB_2A)
VGA_B2: R40.2, RN7.2 (R2.1), U1.48 (IOB_4A)
VGA_B3: R39.2, RN7.1 (R1.1), U1.2 (IOB_6A)
VGA_G0: R38.2, RN4.4 (R4.1), U1.3 (IOB_9B)
VGA_G1: R35.2, RN4.3 (R3.1), U1.4 (IOB_8A)
VGA_G2: R33.2, RN4.2 (R2.1), U1.6 (IOB_13B)
VGA_G3: R31.2, RN4.1 (R1.1), U1.9 (IOB_16A)
VGA_HSYNC: R37.2, U1.44 (IOB_3B_G6)
VGA_R0: R27.2, RN1.4 (R4.1), U1.10 (IOB_18A)
VGA_R1: R25.2, RN1.3 (R3.1), U1.11 (IOB_20A)
VGA_R2: R24.2, RN1.2 (R2.1), U1.12 (IOB_22A)
VGA_R3: R21.2, RN1.1 (R1.1), U1.13 (IOB_24A)
VGA_VSYNC: R34.2, U1.45 (IOB_5B)

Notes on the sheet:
FPGA
25MHz oscillator
Level shifters
Bus connector
Secure Digital Interface
3.3V power supply
1.2V power supply
VGA interface
Composite / S-video interface
Audio output
SPI flash
SPI pins multiplexing

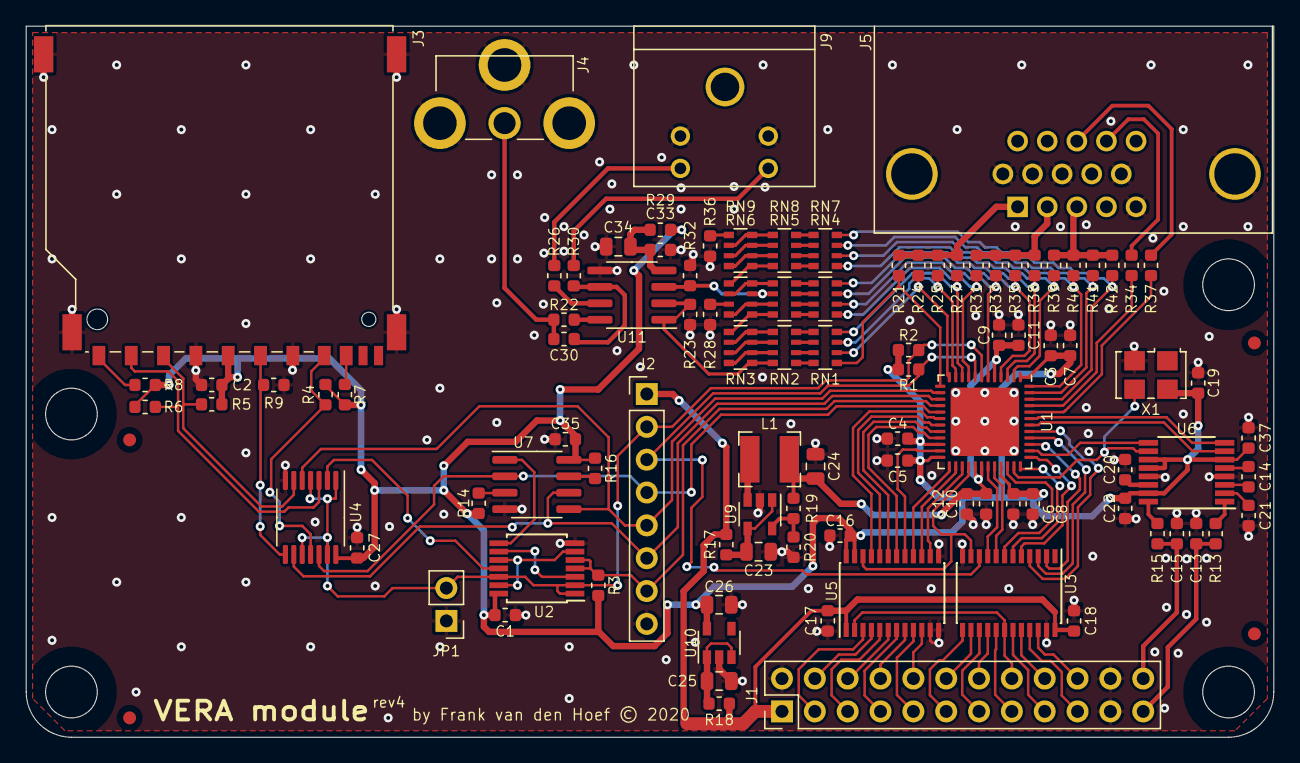
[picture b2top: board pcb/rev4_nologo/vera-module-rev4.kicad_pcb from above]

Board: 2 copper layers, 96.5 x 55.0 mm, 107 parts (0 on the bottom side), 125 nets.

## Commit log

2022-03-14 Removed X16 logo for use in designs other than the Commander X16.
2022-03-15 General cleanup: remove old VERA pcb revs
2022-04-02 VERA with changes for running on UPduino 3.1
2022-07-18 Create Visual Studio 2019 Project for building under windows.
2022-07-22 Removed flash check so that Kevin can flash his VERA.
2022-07-22 Plumbed fifo_empty signal up to top and added it to bit 6 of register 0x1B.
2022-08-31 Added documentation for FIFO empty bit.
2023-01-29 implemented Linked mode
2023-03-21 Rename "line_mode" to "interlace"
2023-07-24 Bump version
2023-07-24 Set version to 0.3.1
2023-11-19 Update with new footprints
2023-11-20 ESD protection and HDMI headers
2023-12-09 Misc panelized PCB changes.
2024-01-20 Fix back to back write issue

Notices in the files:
pcb/rev4/vera-module-rev4.kicad_pcb:
by Frank van den Hoef © 2020
X5 by Joe Burks (C) 2023
pcb/rev4/vera-module-rev4.kicad_sch:
(C) 2020 Frank van den Hoef
